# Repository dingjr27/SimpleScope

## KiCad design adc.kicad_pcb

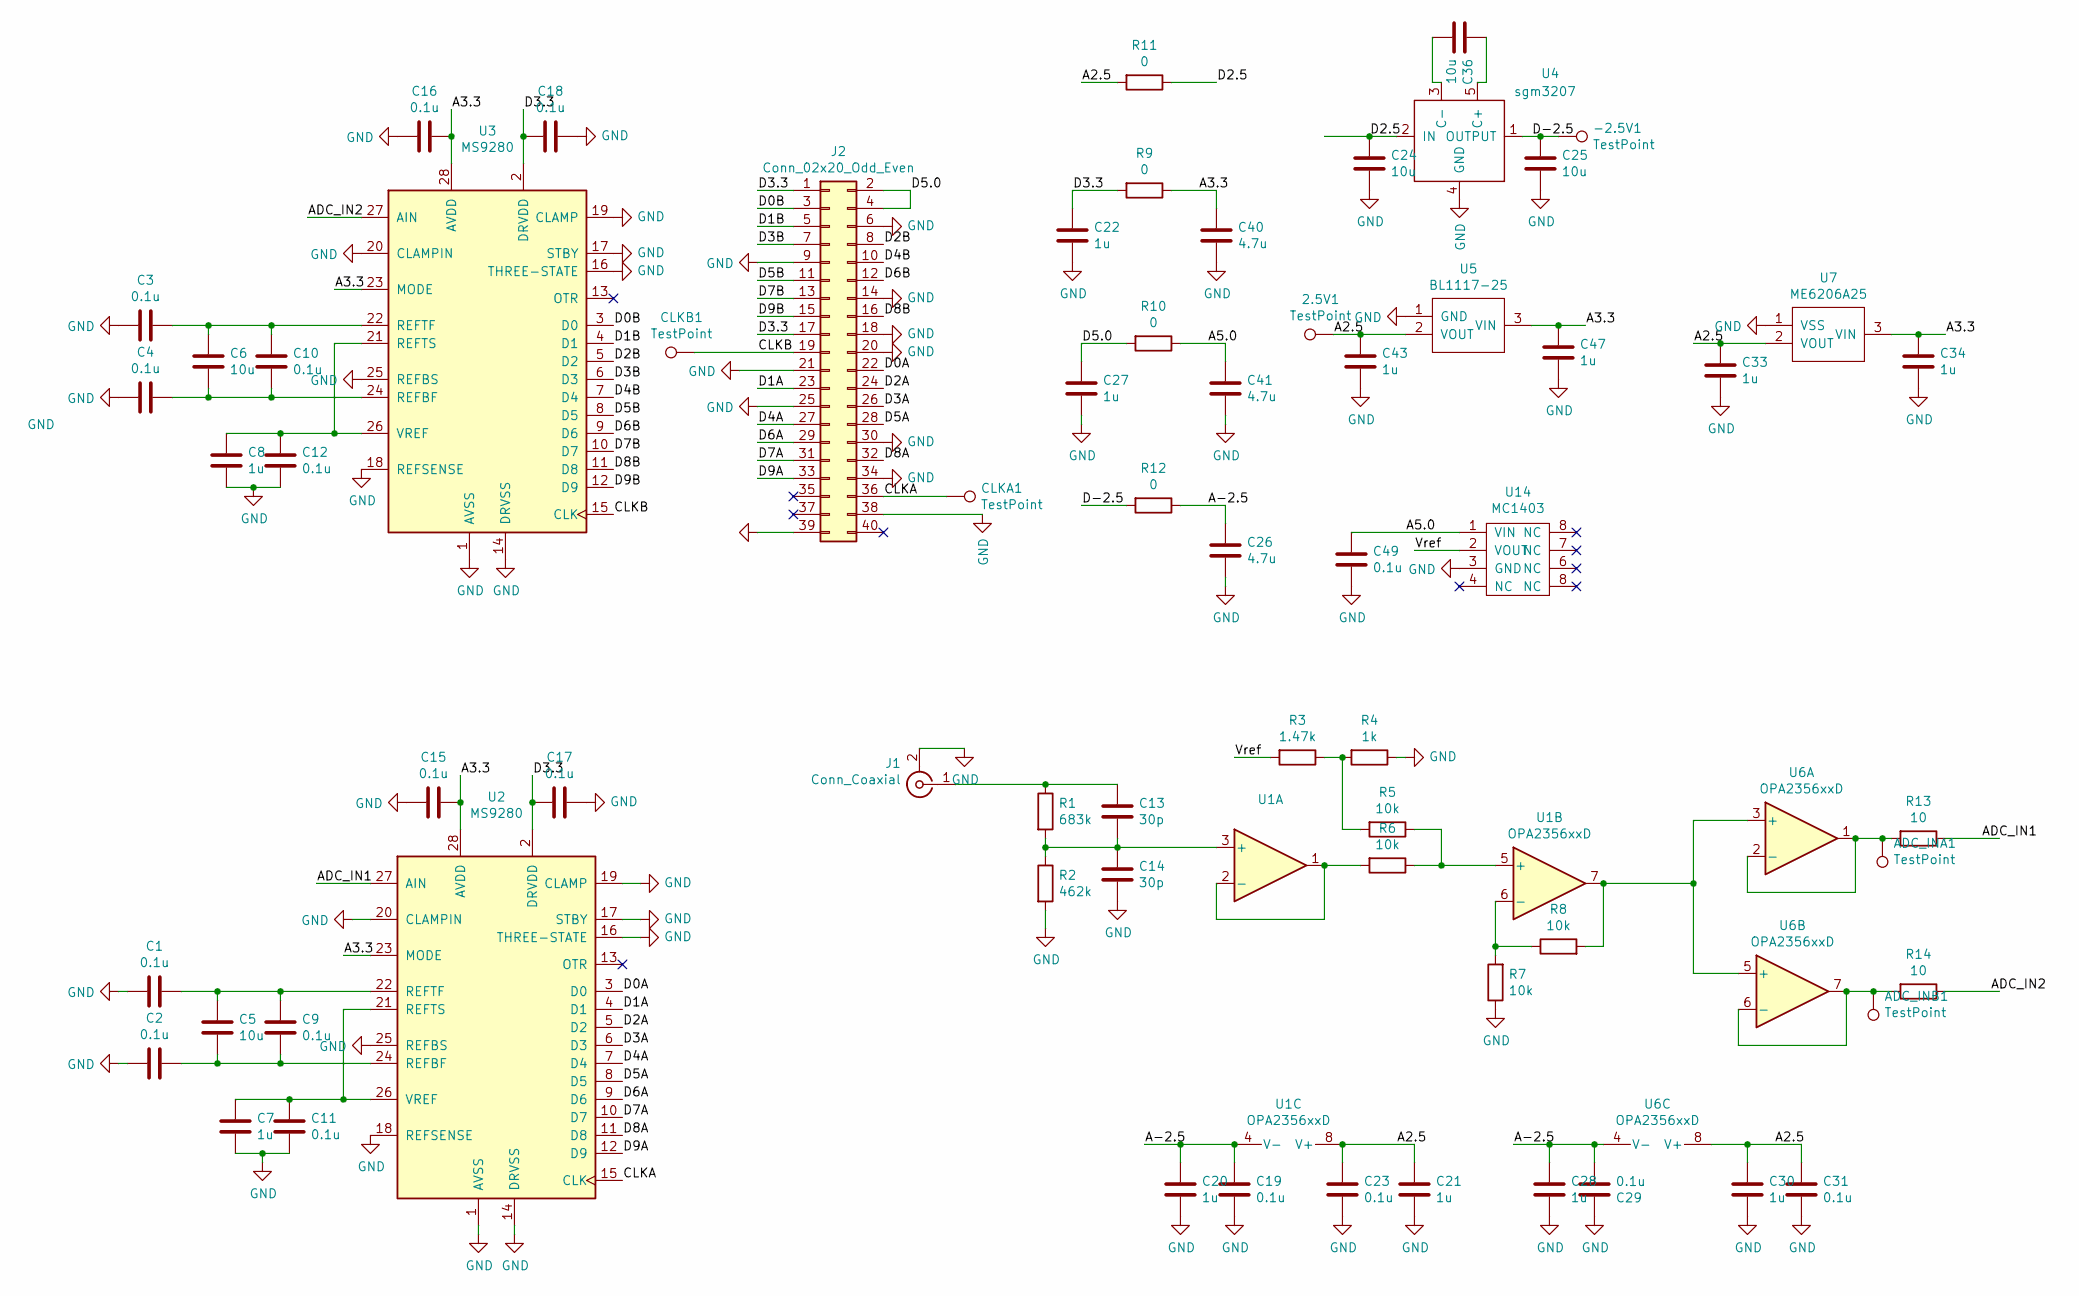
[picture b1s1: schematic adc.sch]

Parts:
2.5V1: TestPoint; TestPoint_Pad_1.0x1.0mm
-2.5V1: TestPoint; TestPoint_Pad_1.0x1.0mm
ADC_INA1: TestPoint; TestPoint_Pad_1.0x1.0mm
ADC_INB1: TestPoint; TestPoint_Pad_1.0x1.0mm
C1, C2, C3, C4, C9, C10, C11, C12, C15, C16, C17, C18, C19, C23, C29, C31, C49: 0.1u; C_0805_2012Metric
C5, C6, C24, C25, C36: 10u; C_0805_2012Metric
C7, C8, C20, C21, C22, C27, C28, C30, C33, C34, C43, C47: 1u; C_0805_2012Metric
C13, C14: 30p; C_0805_2012Metric
C26, C40, C41: 4.7u; C_0805_2012Metric
CLKA1: TestPoint; TestPoint_Pad_1.0x1.0mm
CLKB1: TestPoint; TestPoint_Pad_1.0x1.0mm
J1: Conn_Coaxial; BNC_Amphenol_B6252HB-NPP3G-50_Horizontal
J2: Conn_02x20_Odd_Even; PinHeader_2x20_P2.54mm_Vertical
R1: 683k; R_0805_2012Metric
R2: 462k; R_0805_2012Metric
R3: 1.47k; R_0805_2012Metric
R4: 1k; R_0805_2012Metric
R5, R6, R7, R8: 10k; R_0805_2012Metric
R9, R10, R11, R12: 0; R_0805_2012Metric
R13, R14: 10; R_0805_2012Metric
U1, U6: OPA2356xxD; SOIC-8_5.23x5.23mm_P1.27mm
U2, U3: MS9280; SSOP-28_5.3x10.2mm_P0.65mm
U4: sgm3207; SOT-23-5_HandSoldering
U5: BL1117-25; SOT-223-3_TabPin2
U7: ME6206A25; SOT-23_Handsoldering
U14: MC1403; SOP-8_3.76x4.96mm_P1.27mm

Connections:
/A2.5: 2.5V1.1, C21.1, C23.1, C30.1, C31.1, C33.1, C43.1, R11.2, U1.8 (V+), U5.2 (VOUT), U6.8 (V+), U7.2 (VOUT)
/A3.3: C15.1, C16.1, C34.1, C40.1, C47.1, R9.1, U2.23 (MODE), U2.28 (AVDD), U3.23 (MODE), U3.28 (AVDD), U5.3 (VIN), U7.3 (VIN)
/A5.0: C41.1, C49.1, R10.1, U14.1 (VIN)
/A-2.5: C19.1, C20.1, C26.1, C28.1, C29.2, R12.1, U1.4 (V-), U6.4 (V-)
/ADC_IN1: R13.1, U2.27 (AIN)
/ADC_IN2: R14.1, U3.27 (AIN)
/CLKA: CLKA1.1, J2.36, U2.15 (CLK)
/CLKB: CLKB1.1, J2.19, U3.15 (CLK)
/D0A: J2.22, U2.3 (D0)
/D0B: J2.3, U3.3 (D0)
/D1A: J2.23, U2.4 (D1)
/D1B: J2.5, U3.4 (D1)
/D2.5: C24.1, R11.1, U4.2 (IN)
/D2A: J2.24, U2.5 (D2)
/D2B: J2.8, U3.5 (D2)
/D3.3: C17.2, C18.2, C22.1, J2.1, J2.17, R9.2, U2.2 (DRVDD), U3.2 (DRVDD)
/D3A: J2.26, U2.6 (D3)
/D3B: J2.7, U3.6 (D3)
/D4A: J2.27, U2.7 (D4)
/D4B: J2.10, U3.7 (D4)
/D5.0: C27.1, J2.2, J2.4, R10.2
/D5A: J2.28, U2.8 (D5)
/D5B: J2.11, U3.8 (D5)
/D6A: J2.29, U2.9 (D6)
/D6B: J2.12, U3.9 (D6)
/D7A: J2.31, U2.10 (D7)
/D7B: J2.13, U3.10 (D7)
/D8A: J2.32, U2.11 (D8)
/D8B: J2.16, U3.11 (D8)
/D9A: J2.33, U2.12 (D9)
/D9B: J2.15, U3.12 (D9)
/D-2.5: -2.5V1.1, C25.1, R12.2, U4.1 (OUTPUT)
/Vref: R3.2, U14.2 (VOUT)
GND: C1.2, C2.2, C3.2, C4.2, C7.2, C8.2, C11.2, C12.2, C14.2, C15.2, C16.2, C17.1, C18.1, C19.2, C20.2, C21.2, C22.2, C23.2, C24.2, C25.2, C26.2, C27.2, C28.2, C29.1, C30.2, C31.2, C33.2, C34.2, C40.2, C41.2, C43.2, C47.2, C49.2, J1.2 (Ext), J2.6, J2.9, J2.14, J2.18, J2.20, J2.21, J2.25, J2.30, J2.34, J2.38, J2.39, R2.2, R4.1, R7.1, U2.1 (AVSS), U2.14 (DRVSS), U2.16 (THREE-STATE), U2.17 (STBY), U2.18 (REFSENSE), U2.19 (CLAMP), U2.20 (CLAMPIN), U2.25 (REFBS), U3.1 (AVSS), U3.14 (DRVSS), U3.16 (THREE-STATE), U3.17 (STBY), U3.18 (REFSENSE), U3.19 (CLAMP), U3.20 (CLAMPIN), U3.25 (REFBS), U4.4 (GND), U5.1 (GND), U7.1 (VSS), U14.3 (GND)
unnamed: ADC_INA1.1, R13.2, U6.1, U6.2 (-)
unnamed: ADC_INB1.1, R14.2, U6.6 (-), U6.7
unnamed: C1.1, C5.1, C9.1, U2.22 (REFTF)
unnamed: C2.1, C5.2, C9.2, U2.24 (REFBF)
unnamed: C3.1, C6.1, C10.1, U3.22 (REFTF)
unnamed: C4.1, C6.2, C10.2, U3.24 (REFBF)
unnamed: C7.1, C11.1, U2.21 (REFTS), U2.26 (VREF)
unnamed: C8.1, C12.1, U3.21 (REFTS), U3.26 (VREF)
unnamed: C13.1, J1.1 (In), R1.1
unnamed: C13.2, C14.1, R1.2, R2.1, U1.3 (+)
unnamed: C36.1, U4.5 (C+)
unnamed: C36.2, U4.3 (C-)
unnamed: R3.1, R4.2, R5.2
unnamed: R5.1, R6.1, U1.5 (+)
unnamed: R6.2, U1.1, U1.2 (-)
unnamed: R7.2, R8.1, U1.6 (-)
unnamed: R8.2, U1.7, U6.3 (+), U6.5 (+)

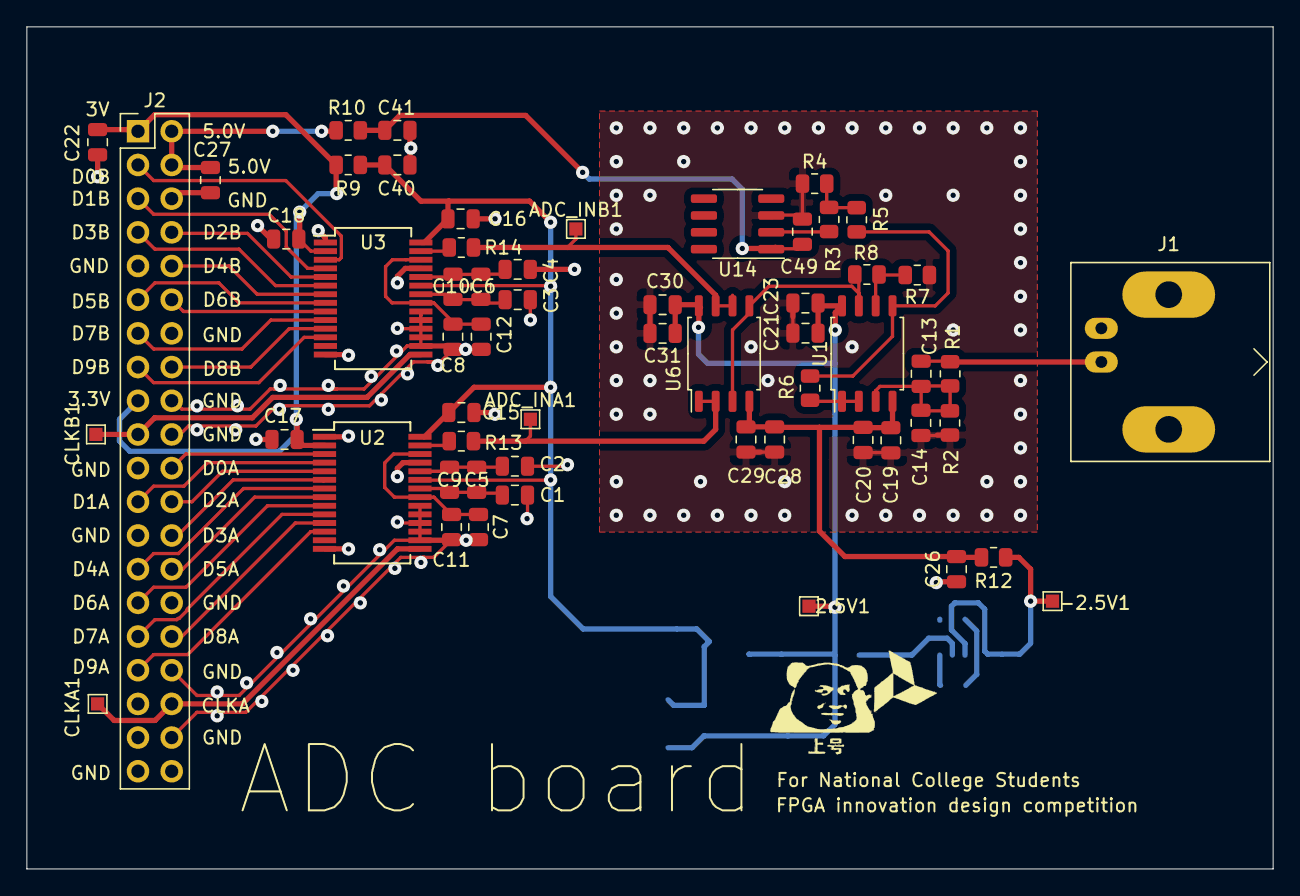
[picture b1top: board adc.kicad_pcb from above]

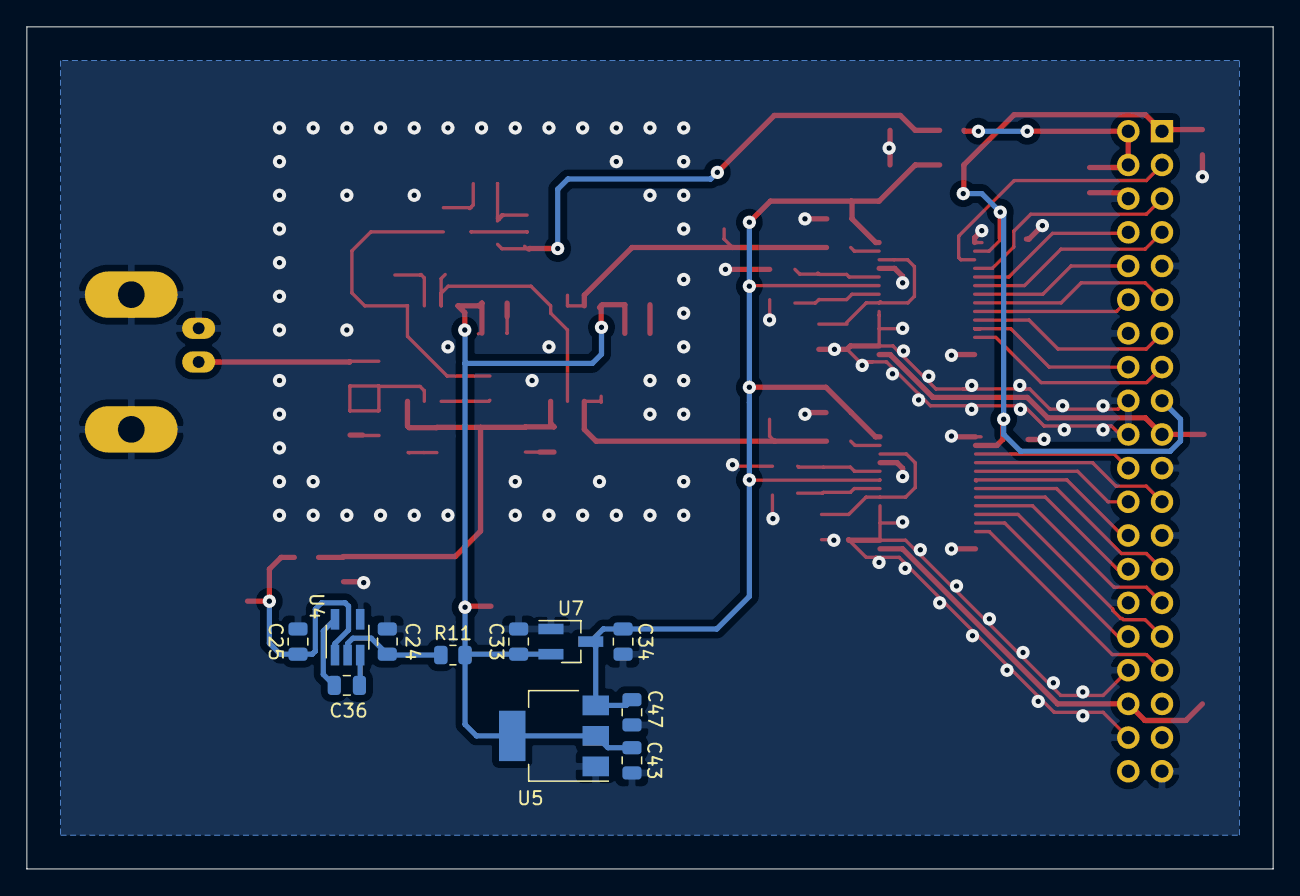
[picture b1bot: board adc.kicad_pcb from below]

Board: 2 copper layers, 94.0 x 63.5 mm, 69 parts (11 on the bottom side), 51 nets.

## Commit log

2021-11-08 hello world
